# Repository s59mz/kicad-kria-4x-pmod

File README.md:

# kicad-kria-4x-pmod
Adapter for Kria KR260 board for 4xPMOD interfaces

Schematic:
[kicad-kria-4x-pmod.pdf](kicad-kria-4x-pmod.pdf)

BOM:
[kicad-kria-4x-pmod.csv](kicad-kria-4x-pmod.csv)

Gerbers:
[gerbers.zip](https://github.com/s59mz/kicad-kria-4x-pmod/raw/main/gerbers.zip)

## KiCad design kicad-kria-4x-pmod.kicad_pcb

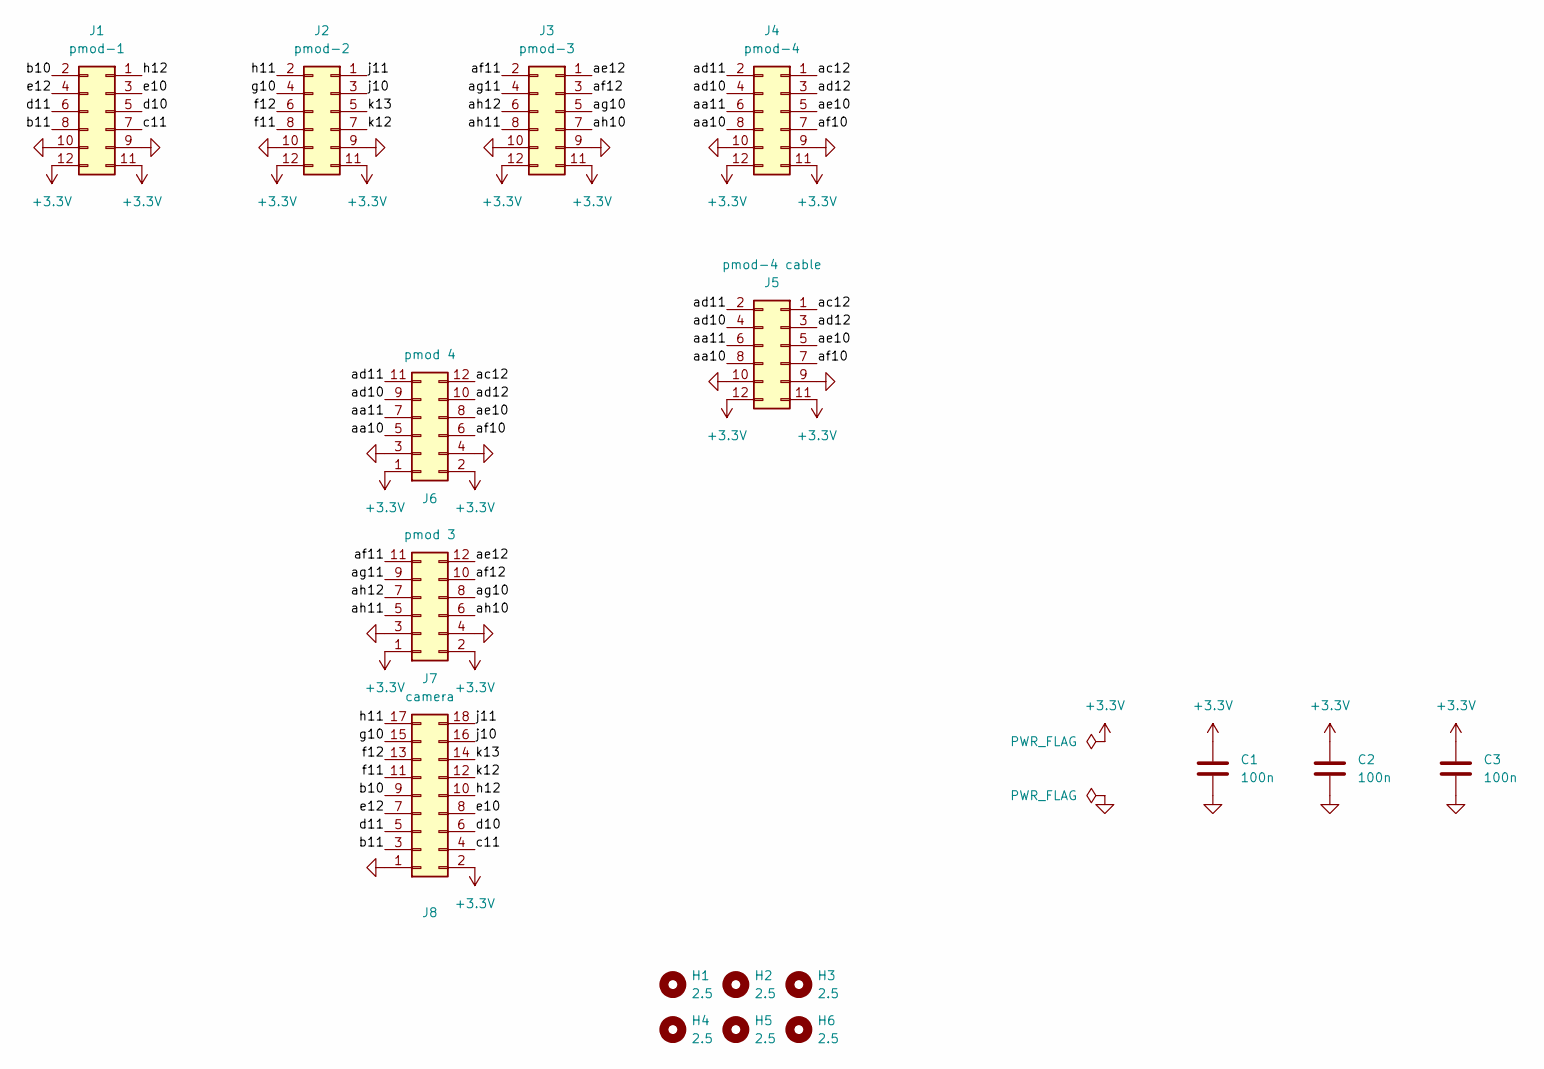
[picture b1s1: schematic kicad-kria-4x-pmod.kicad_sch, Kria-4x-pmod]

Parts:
C1, C2, C3: 100n; C_0603_1608Metric_Pad1.08x0.95mm_HandSolder
H1, H2, H3, H4, H5, H6: 2.5; MountingHole_2.5mm
J1: pmod-1; PinHeader_2x06_P2.54mm_Horizontal
J2: pmod-2; PinHeader_2x06_P2.54mm_Horizontal
J3: pmod-3; PinHeader_2x06_P2.54mm_Horizontal
J4: pmod-4; PinHeader_2x06_P2.54mm_Horizontal
J5: pmod-4 cable; IDC-Header_2x06_P2.54mm_Vertical
J6: pmod 4; PinSocket_2x06_P2.54mm_Horizontal
J7: pmod 3; PinSocket_2x06_P2.54mm_Horizontal
J8: camera; PinSocket_2x09_P2.54mm_Horizontal

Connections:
+3.3V: C1.1, C2.1, C3.1, J1.11, J1.12, J2.11, J2.12, J3.11, J3.12, J4.11, J4.12, J5.11, J5.12, J6.1, J6.2, J7.1, J7.2, J8.2
/aa10: J4.8, J5.8, J6.5
/aa11: J4.6, J5.6, J6.7
/ac12: J4.1, J5.1, J6.12
/ad10: J4.4, J5.4, J6.9
/ad11: J4.2, J5.2, J6.11
/ad12: J4.3, J5.3, J6.10
/ae10: J4.5, J5.5, J6.8
/ae12: J3.1, J7.12
/af10: J4.7, J5.7, J6.6
/af11: J3.2, J7.11
/af12: J3.3, J7.10
/ag10: J3.5, J7.8
/ag11: J3.4, J7.9
/ah10: J3.7, J7.6
/ah11: J3.8, J7.5
/ah12: J3.6, J7.7
/b10: J1.2, J8.9
/b11: J1.8, J8.3
/c11: J1.7, J8.4
/d10: J1.5, J8.6
/d11: J1.6, J8.5
/e10: J1.3, J8.8
/e12: J1.4, J8.7
/f11: J2.8, J8.11
/f12: J2.6, J8.13
/g10: J2.4, J8.15
/h11: J2.2, J8.17
/h12: J1.1, J8.10
/j10: J2.3, J8.16
/j11: J2.1, J8.18
/k12: J2.7, J8.12
/k13: J2.5, J8.14
GND: C1.2, C2.2, C3.2, J1.9, J1.10, J2.9, J2.10, J3.9, J3.10, J4.9, J4.10, J5.9, J5.10, J6.3, J6.4, J7.3, J7.4, J8.1

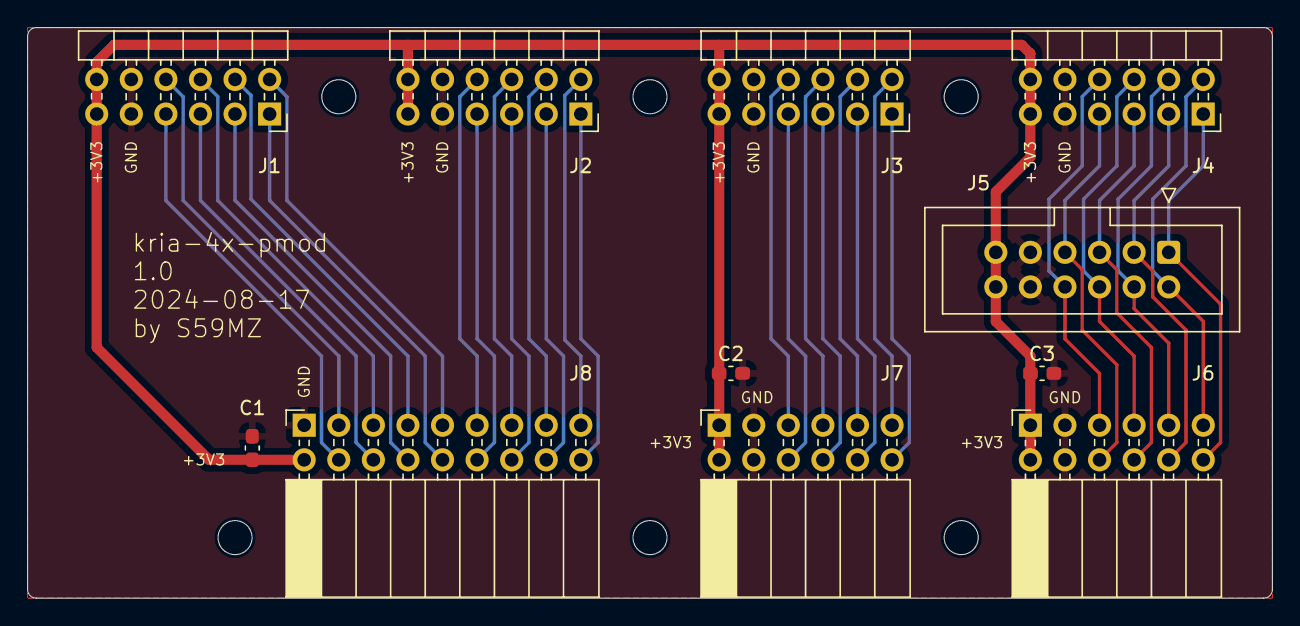
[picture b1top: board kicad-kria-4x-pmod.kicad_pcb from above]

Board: 2 copper layers, 91.4 x 41.9 mm, 17 parts (0 on the bottom side), 34 nets.
